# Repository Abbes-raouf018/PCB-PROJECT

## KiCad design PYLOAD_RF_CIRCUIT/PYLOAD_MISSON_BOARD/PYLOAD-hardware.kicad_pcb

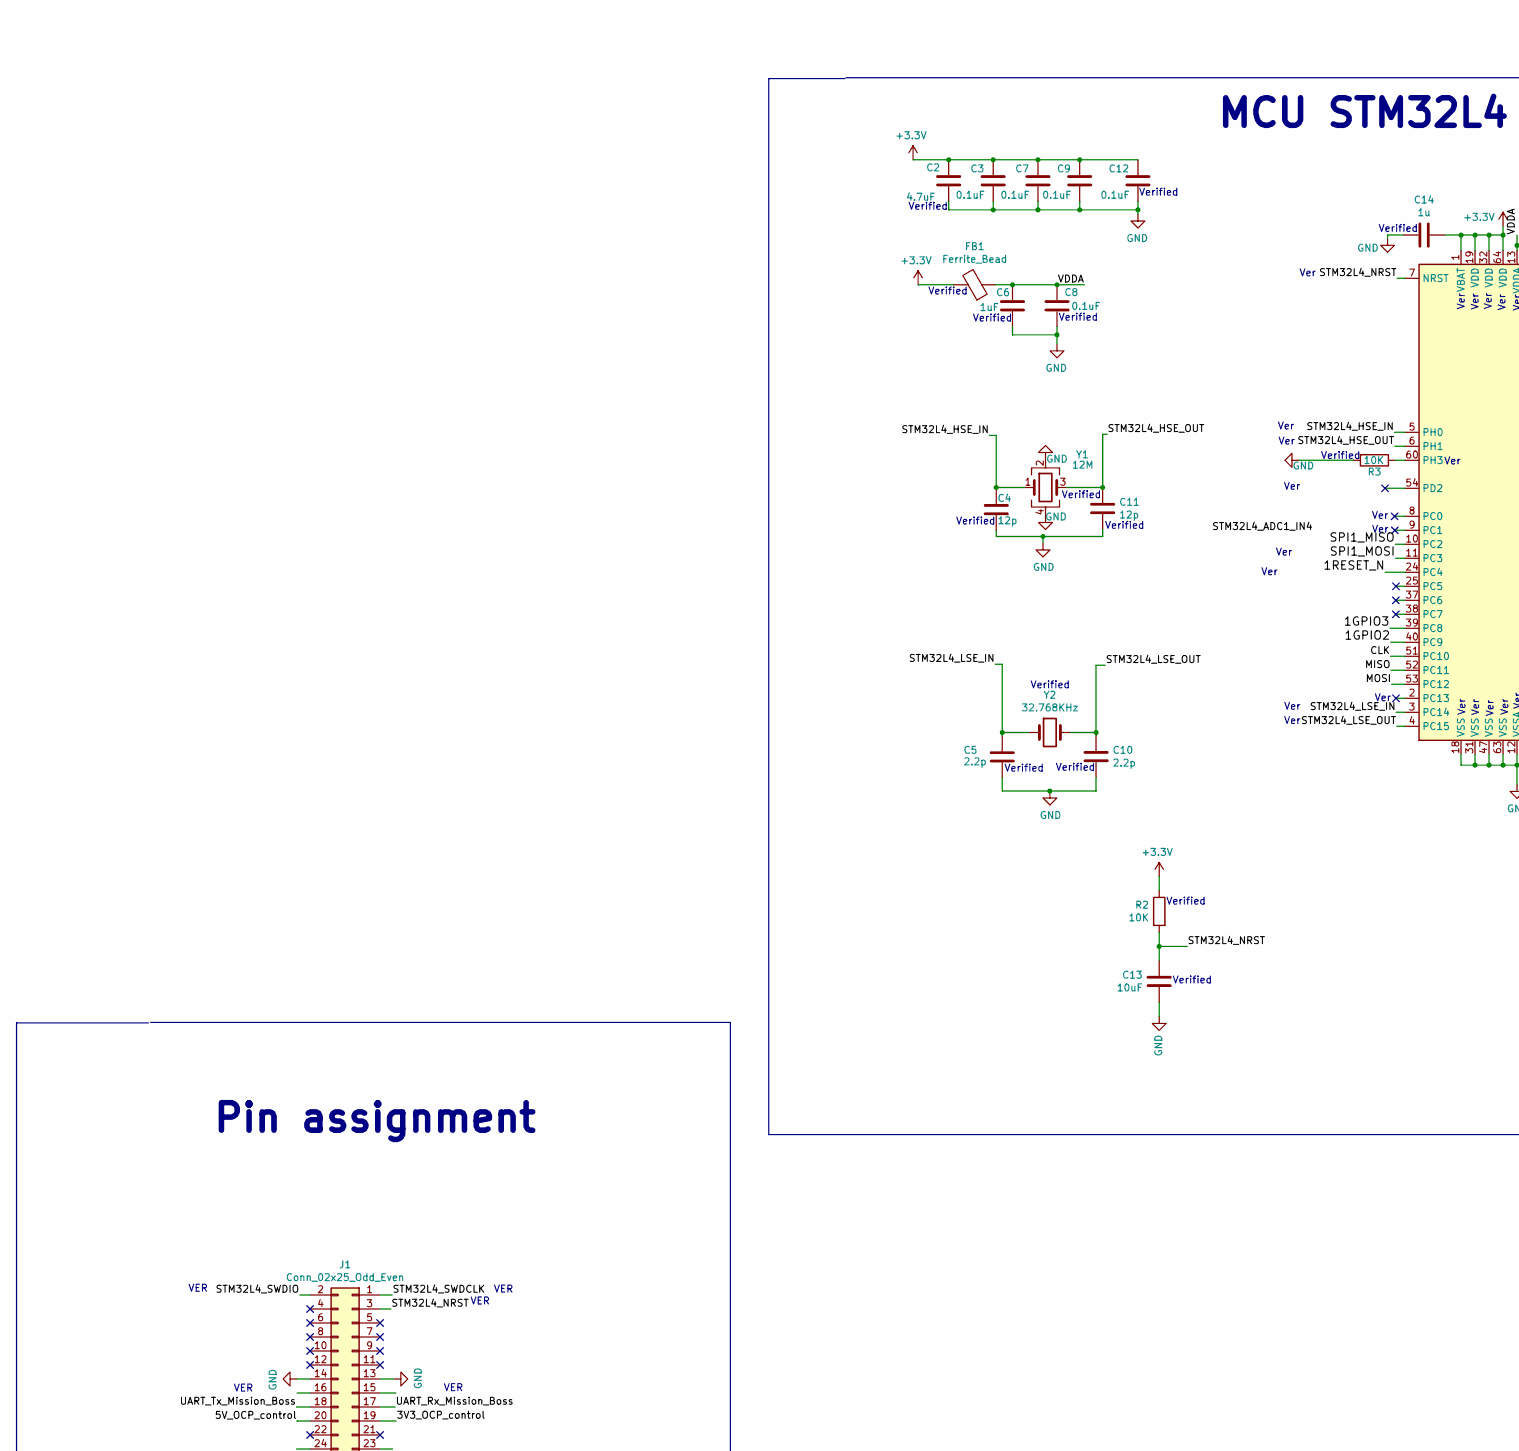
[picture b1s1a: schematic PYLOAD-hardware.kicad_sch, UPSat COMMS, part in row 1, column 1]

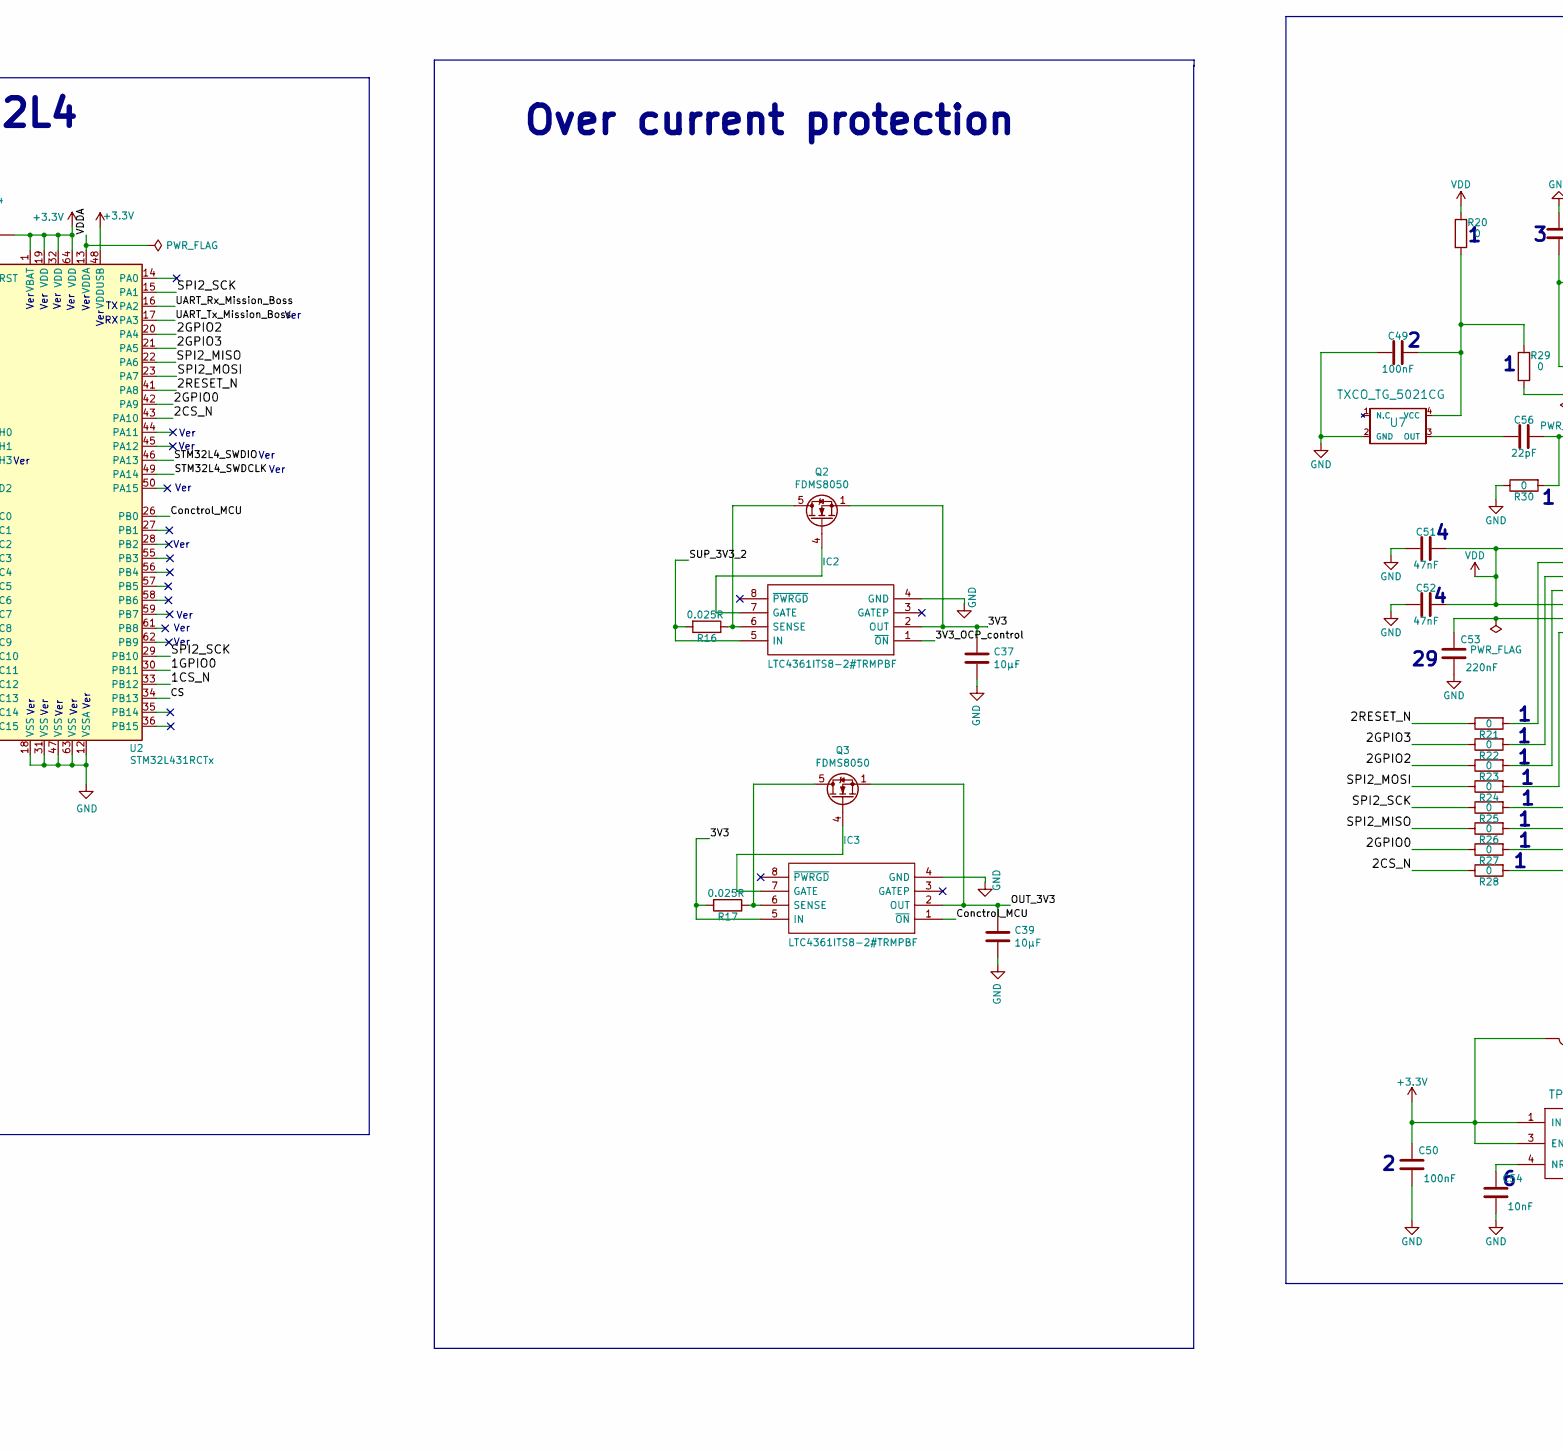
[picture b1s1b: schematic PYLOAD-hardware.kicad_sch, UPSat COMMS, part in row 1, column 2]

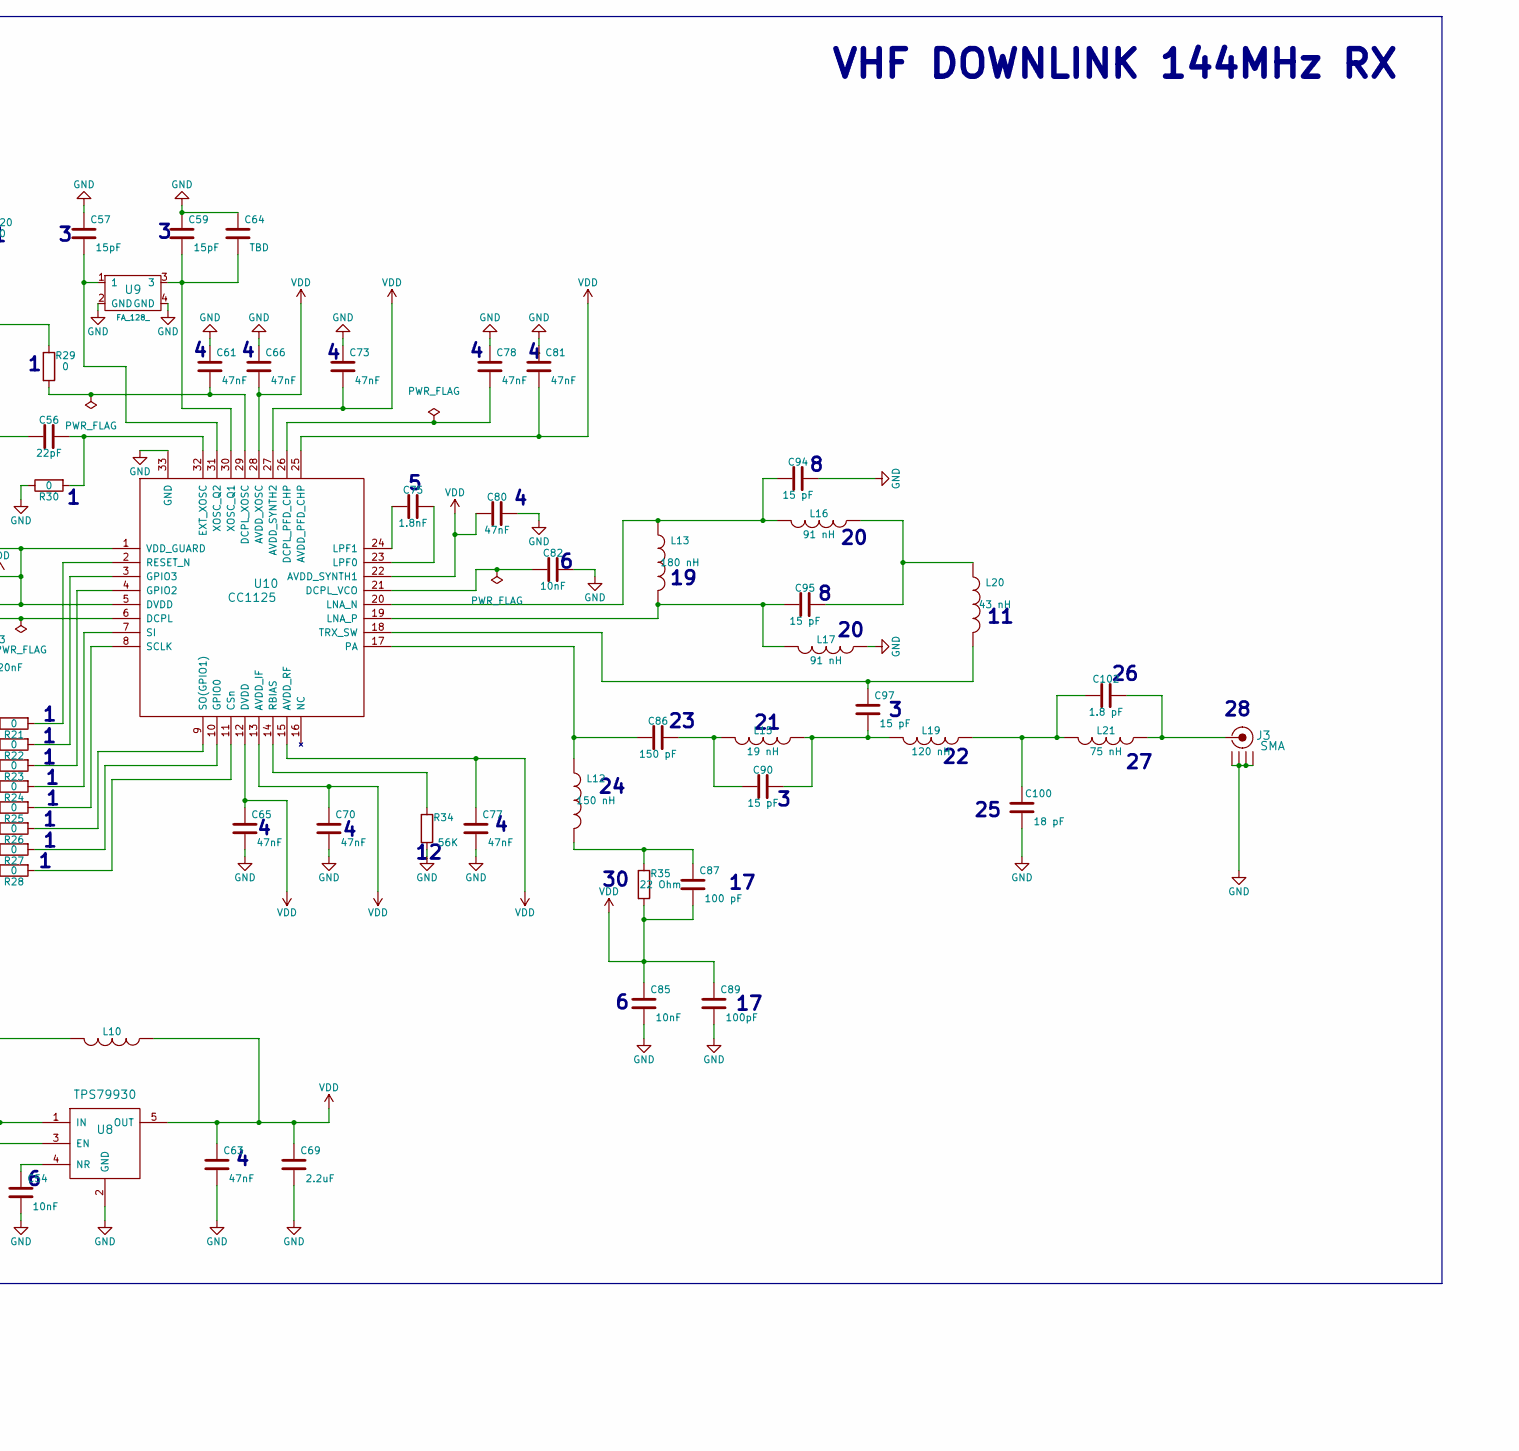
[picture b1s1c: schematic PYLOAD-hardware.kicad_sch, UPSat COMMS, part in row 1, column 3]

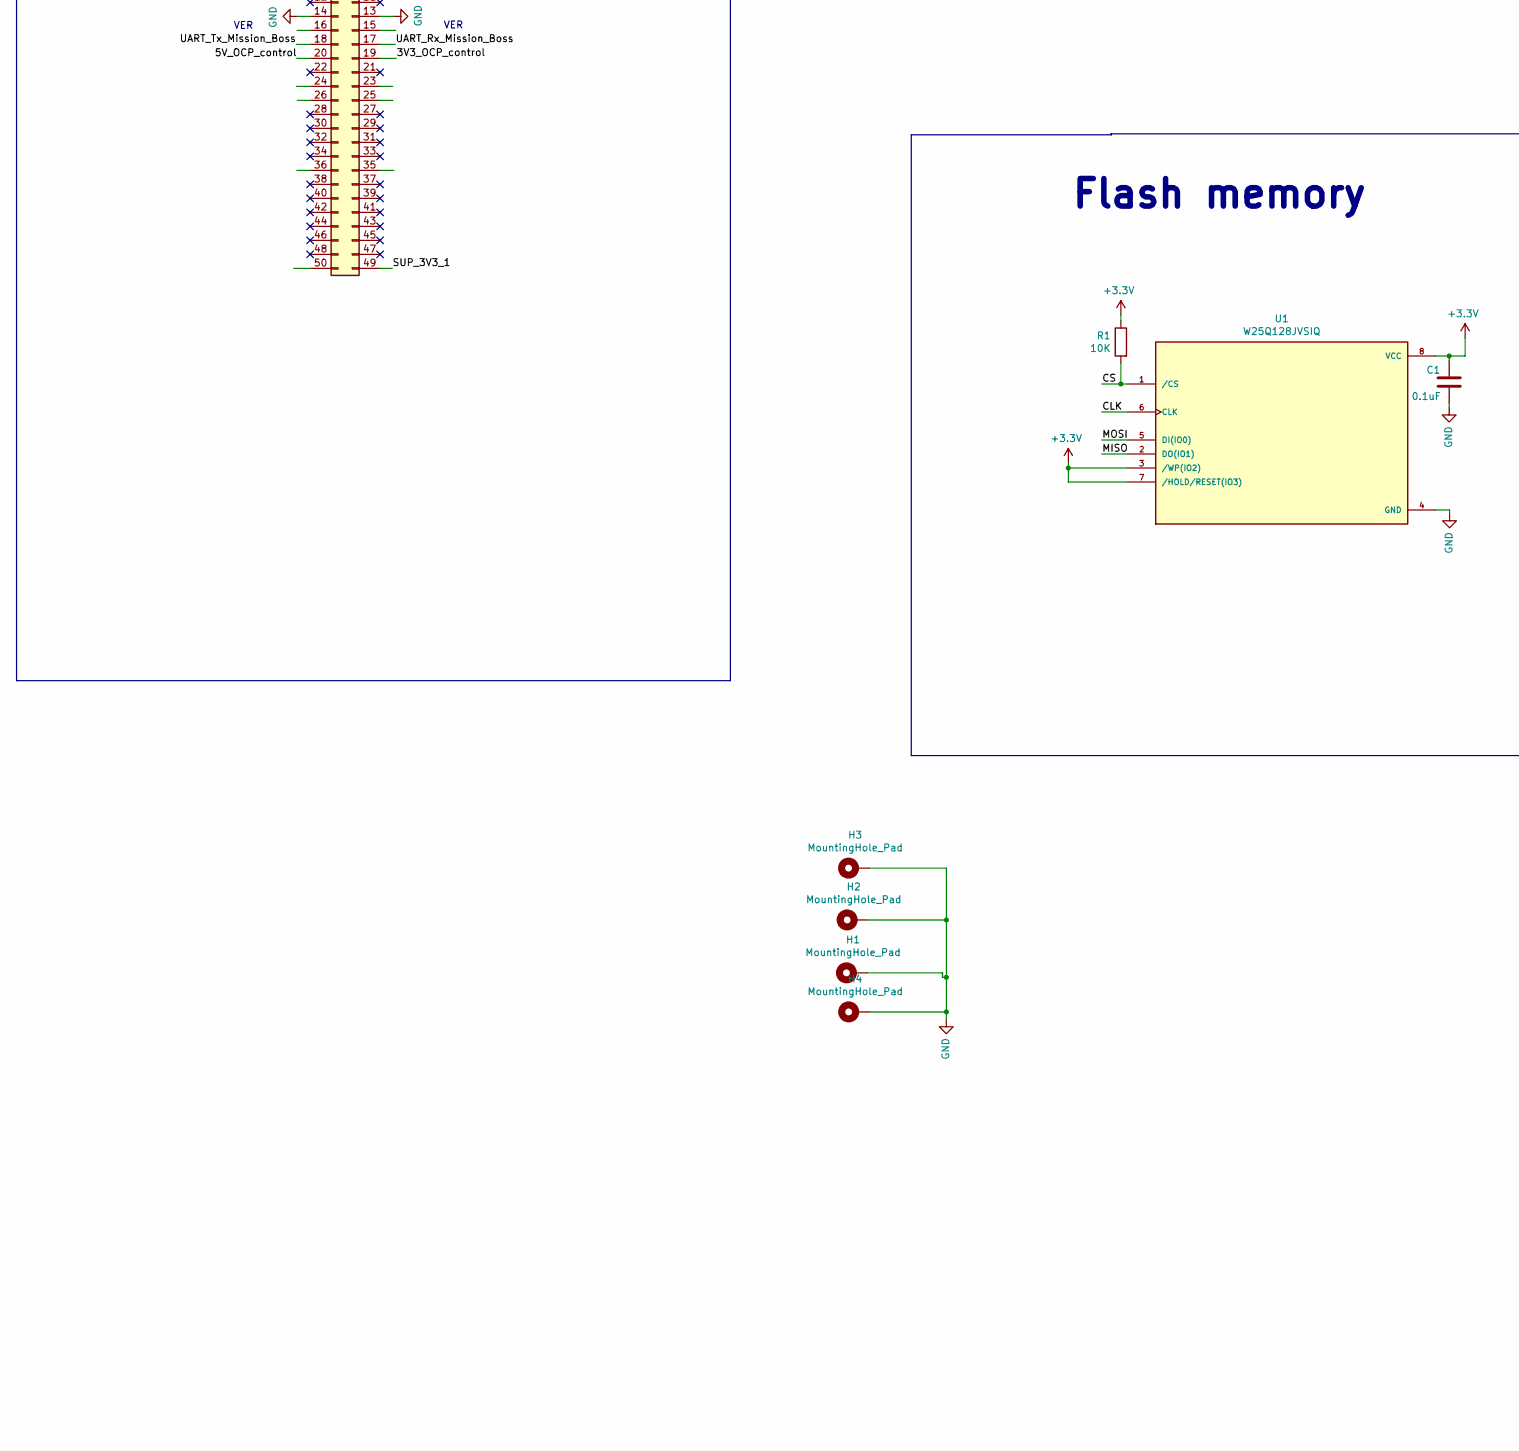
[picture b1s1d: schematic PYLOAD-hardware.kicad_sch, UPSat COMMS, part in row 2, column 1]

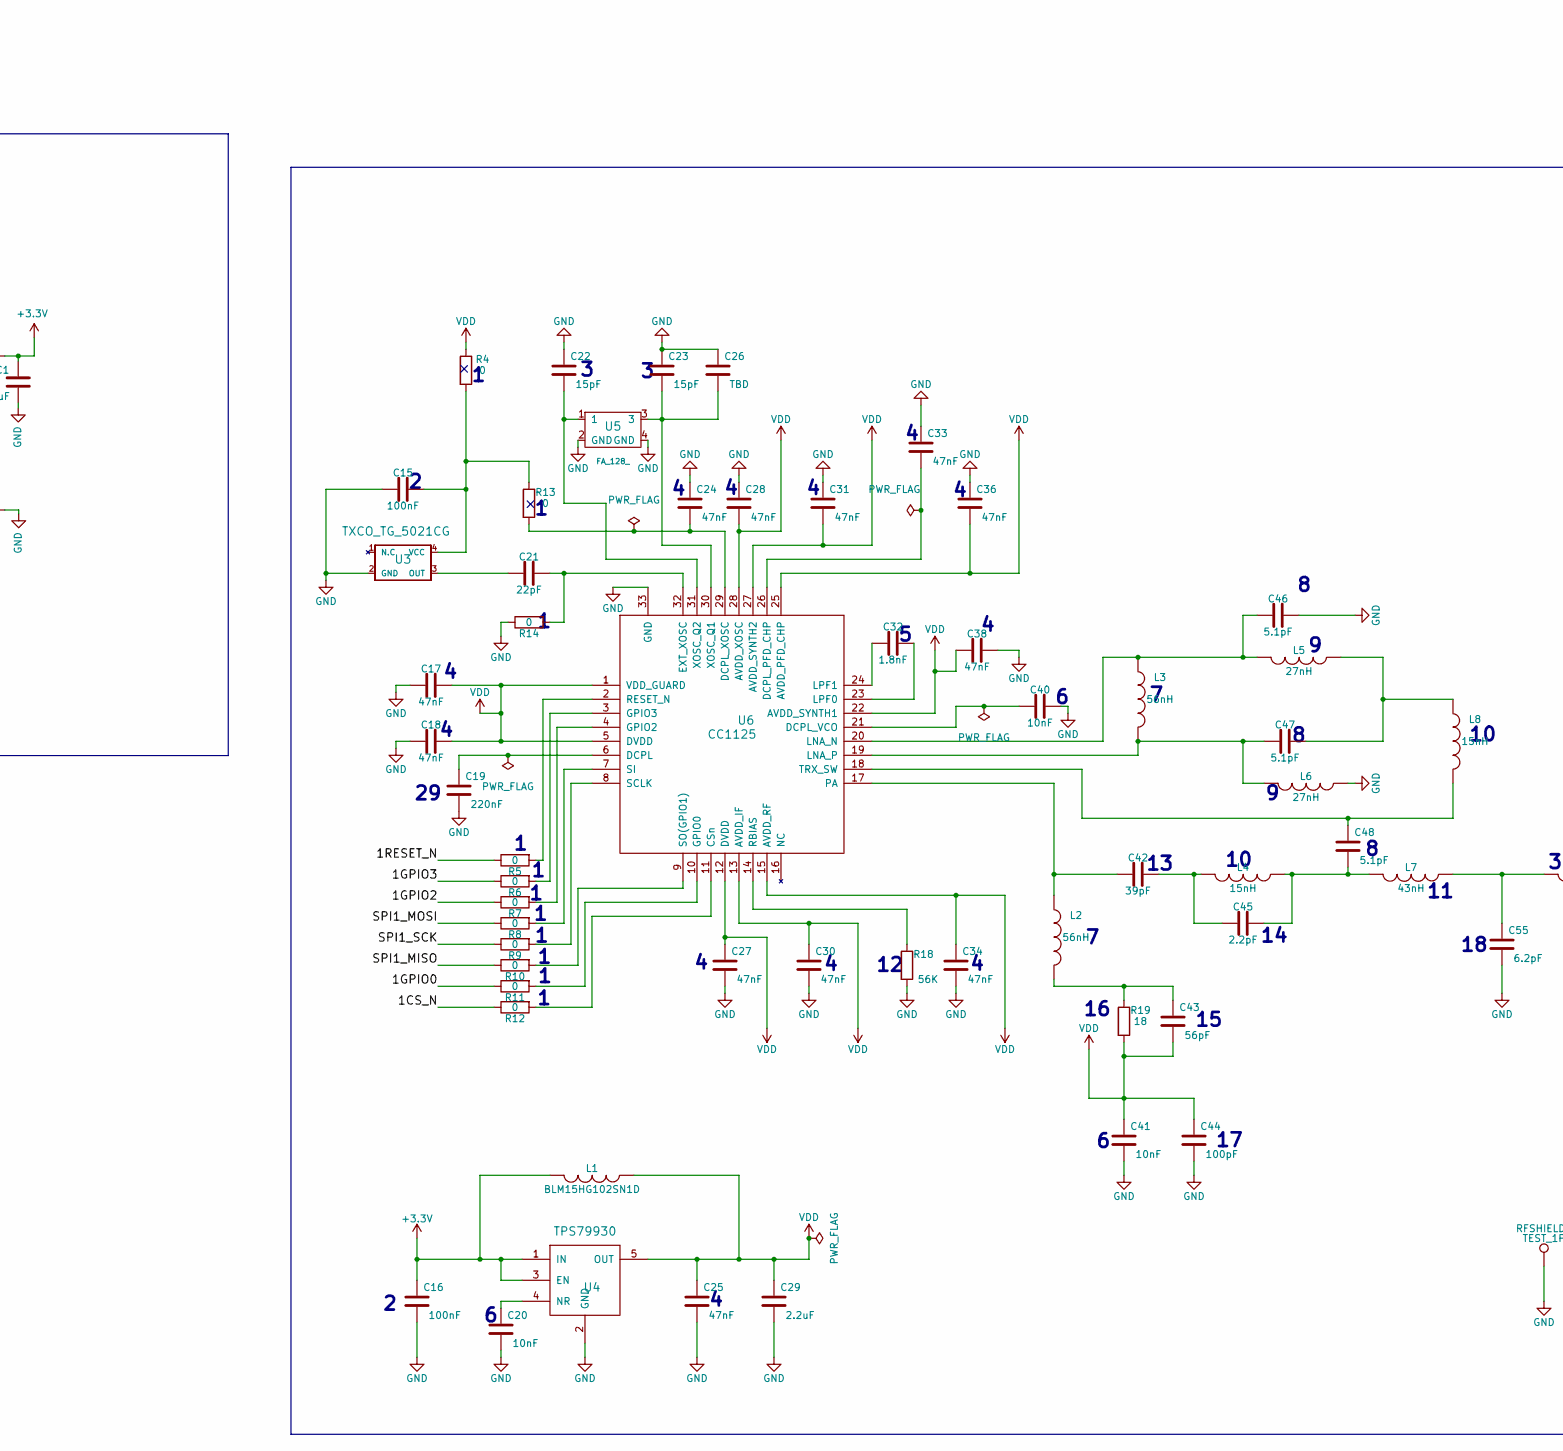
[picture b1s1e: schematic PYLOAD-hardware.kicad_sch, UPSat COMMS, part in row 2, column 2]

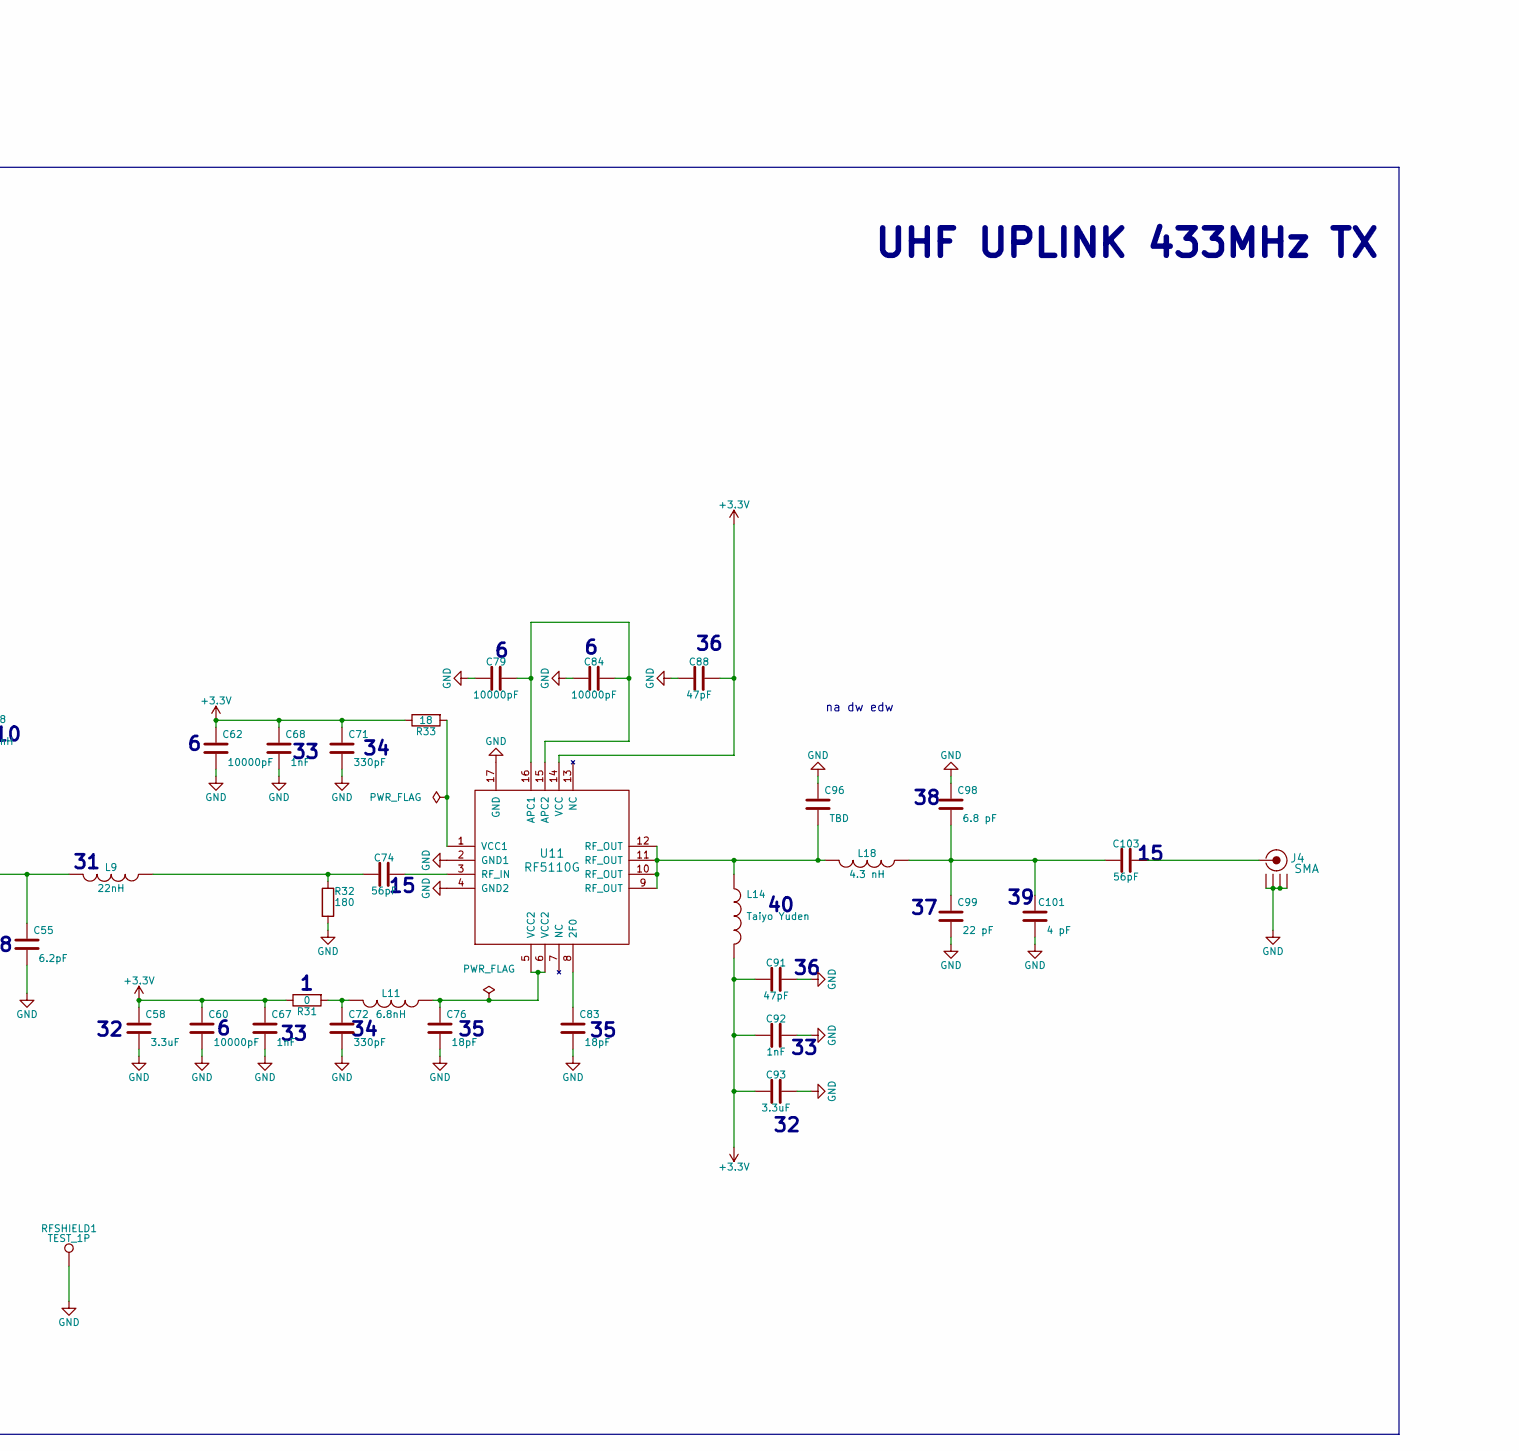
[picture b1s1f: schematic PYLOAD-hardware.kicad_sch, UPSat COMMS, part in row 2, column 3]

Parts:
C1, C3, C7, C9: 0.1uF; C_0402_1005Metric; lCSC C1525
C2: 4.7uF; C_0402_1005Metric; LCSC C23733
C4, C11: 12p; C_0402_1005Metric; LCSC C1547
C5, C10: 2.2p; C_0402_1005Metric; LCSC C1559
C6: 1uF; C_0402_1005Metric; LCSC C52923
C8, C12: 0.1uF; C_0402_1005Metric; LCSC C1525
C13: 10uF; C_0805_2012Metric; LCSC C440198
C14: 1u; C_0402_1005Metric; LCSC C52923
C15, C16, C49, C50: 100nF; C_0402_1005Metric; LCSC C1525
C17, C18, C24, C25, C27, C28, C30, C31, C33, C34, C36, C38, C51, C52, C61, C63, C65, C66, C70, C73, C77, C78, C80, C81: 47nF; C_0402_1005Metric; LCSC C1525
C19, C53: 220nF; C_0402_1005Metric; LCSC C1525
C20, C40, C41, C54, C82, C85: 10nF; C_0402_1005Metric; LCSC C1525
C21, C56: 22pF; C_0402_1005Metric; LCSC C1525
C22, C23, C57, C59: 15pF; C_0402_1005Metric; LCSC C1525
C26, C64, C96: TBD; C_0402_1005Metric; LCSC C1525
C29, C69: 2.2uF; C_0603_1608Metric; LCSC C1679
C32, C75: 1.8nF; C_0402_1005Metric; LCSC C1525
C37, C39: 10µF; C_0402_1005Metric; LCSC C1547
C42: 39pF; C_0402_1005Metric; LCSC C1525
C43, C74, C103: 56pF; C_0402_1005Metric; LCSC C1525
C44, C89: 100pF; C_0402_1005Metric; LCSC C1525
C45: 2.2pF; C_0402_1005Metric; LCSC C1525
C46, C47, C48: 5.1pF; C_0402_1005Metric; LCSC C1525
C55: 6.2pF; C_0402_1005Metric; LCSC C1525
C58, C93: 3.3uF; C_0402_1005Metric; LCSC C1525
C60, C62, C79, C84: 10000pF; C_0402_1005Metric; LCSC C1525
C67, C68, C92: 1nF; C_0402_1005Metric; LCSC C1525
C71, C72: 330pF; C_0402_1005Metric; LCSC C1525
C76, C83: 18pF; C_0402_1005Metric; LCSC C1525
C86: 150 pF; C_0402_1005Metric; LCSC C1525
C87: 100 pF; C_0402_1005Metric; LCSC C1525
C88, C91: 47pF; C_0402_1005Metric; LCSC C1525
C90, C94, C95, C97: 15 pF; C_0402_1005Metric; LCSC C1525
C98: 6.8 pF; C_0402_1005Metric; LCSC C1525
C99: 22 pF; C_0402_1005Metric; LCSC C1525
C100: 18 pF; C_0402_1005Metric; LCSC C1525
C101: 4 pF; C_0402_1005Metric; LCSC C1525
C102: 1.8 pF; C_0402_1005Metric; LCSC C1525
FB1: Ferrite_Bead; L_0603_1608Metric; LCSC C20345
H1, H2, H3, H4: MountingHole_Pad; MountingHole_3.7mm
IC2, IC3: LTC4361ITS8-2#TRMPBF; Mouser Part Number 584-C4361ITS8-2TMPF
J1: Conn_02x25_Odd_Even; HDR-TH_50P-P2.00-V-M-R2-C25-S2.00; LCSC C725937
J3, J4: SMA; 60611002111502
L1: BLM15HG102SN1D; C_0402_1005Metric; LCSC C76889
L2, L3: 56nH; L_01005_0402Metric; LCSC C76889
L4: 15nH; L_01005_0402Metric; LCSC C76899
L5, L6: 27nH; L_01005_0402Metric; LCSC C76889
L7: 43nH; L_01005_0402Metric; LCSC C76889
L8: 15nH; L_01005_0402Metric; LCSC C76889
L9: 22nH; L_01005_0402Metric; LCSC C76889
L10: Capacitor_SMD:C_0402_1005Metric; C_0402_1005Metric; LCSC C76889
L11: 6.8nH; L_01005_0402Metric; LCSC C76889
L12: 150 nH; L_01005_0402Metric; LCSC C76889
L13: 180 nH; L_01005_0402Metric; LCSC C76889
L14: Taiyo Yuden; L_01005_0402Metric; LCSC C76889
L15: 19 nH; L_01005_0402Metric; LCSC C76889
L16, L17: 91 nH; L_01005_0402Metric; LCSC C76889
L18: 4.3 nH; L_01005_0402Metric; LCSC C76889
L19: 120 nH; L_01005_0402Metric; LCSC C76889
L20: 43 nH; L_01005_0402Metric; LCSC C76889
L21: 75 nH; L_01005_0402Metric; LCSC C76889
Q2: FDMS8050; MOSFET_C124530_JLCPCB_REVERSE-POLARITY.kicad_mod; LCSC C150470
Q3: FDMS8050; SOT-323_SC-70; LCSC C150470
R1, R2, R3: 10K; R_0603_1608Metric; LCSC C25804
R4, R5, R6, R7, R8, R9, R10, R11, R12, R13, R14, R20, R21, R22, R23, R24, R25, R26, R27, R28, R30, R31: 0; R_0402_1005Metric; LCSC C25120
R16, R17: 0.025R; R_0603_1608Metric; LCSC C25804
R18, R34: 56K; R_0402_1005Metric; LCSC C25120
R19, R33: 18; R_0402_1005Metric; LCSC C25120
R29: 0; R_0402_1005Metric
R32: 180; R_0402_1005Metric; LCSC C25120
R35: 22 Ohm; R_0402_1005Metric; LCSC C25120
RFSHIELD1: TEST_1P; BMI-S-x06
U1: W25Q128JVSIQ; FLAHMEMORY; PARTREV I; LCSC C97521
U2: STM32L431RCTx; LQFP-64_10x10mm_P0.5mm; LCSC C92468
U3, U7: TXCO_TG_5021CG; Crystal_SMD_3225-4Pin_3.2x2.5mm; LCSC C50430
U4, U8: TPS79930; TSOT-23-5_L2.9-W1.6-P0.95-LS2.8-BL; LCSC C201712
U5, U9: FA_128_; Crystal_SMD_3225-4Pin_3.2x2.5mm; LCSC C50430
U6, U10: CC1125; HVQFN-32_L5.0-W5.0-P0.50-TL-EP; LCSC C133234
U11: RF5110G; QFN-16_L3.0-W3.0-P0.50-BL-EP1.5; LCSC C471155
Y1: 12M; Crystal_SMD_3225-4Pin_3.2x2.5mm; LCSC C50430
Y2: 32.768KHz; Crystal_SMD_3215-2Pin_3.2x1.5mm; LCSC C94673

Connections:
+3V3: C1.1, C2.1, C3.1, C7.1, C9.1, C12.1, C14.1, C16.1, C50.1, C58.1, C60.1, C62.1, C67.1, C68.1, C71.1, C88.1, C91.2, C92.2, C93.2, FB1.2, L1.2, L10.2, L14.2, R1.1, R2.1, R31.1, R33.1, U1.3 (/WP(IO2)), U1.7 (/HOLD/RESET(IO3)), U1.8 (VCC), U2.1 (VBAT), U2.19 (VDD), U2.32 (VDD), U2.48 (VDDUSB), U2.64 (VDD), U4.1 (IN), U4.3 (EN), U8.1 (IN), U8.3 (EN), U11.14 (VCC)
/1CS_N: R12.1, U2.33 (PB12)
/1GPIO0: R11.1, U2.30 (PB11)
/1GPIO2: R7.1, U2.40 (PC9)
/1GPIO3: R6.1, U2.39 (PC8)
/1RESET_N: R5.1, U2.24 (PC4)
/2CS_N: R28.1, U2.43 (PA10)
/2GPIO0: R27.1, U2.42 (PA9)
/2GPIO2: R23.1, U2.20 (PA4)
/2GPIO3: R22.1, U2.21 (PA5)
/2RESET_N: R21.1, U2.41 (PA8)
/3V3: C37.1, IC2.2 (OUT), IC3.5 (IN), Q2.1 (S), Q2.2 (S), Q2.3 (S), R17.2
/3V3_OCP_control: IC2.1 (~ON), J1.19
/5V_OCP_control: J1.20
/CLK: U1.6 (CLK), U2.51 (PC10)
/CS: R1.2, U1.1 (/CS), U2.34 (PB13)
/Conctrol_MCU: IC3.1 (~ON), U2.26 (PB0)
/MISO: U1.2 (DO(IO1)), U2.52 (PC11)
/MOSI: U1.5 (DI(IO0)), U2.53 (PC12)
/OUT_3V3: C39.1, IC3.2 (OUT), Q3.1 (S), Q3.2 (S), Q3.3 (S)
/SPI1_MISO: R10.1, U2.10 (PC2)
/SPI1_MOSI: R8.1, U2.11 (PC3)
/SPI1_SCK: R9.1
/SPI2_MISO: R26.1, U2.22 (PA6)
/SPI2_MOSI: R24.1, U2.23 (PA7)
/SPI2_SCK: R25.1, U2.15 (PA1), U2.29 (PB10)
/STM32L4_HSE_IN: C4.1, U2.5 (PH0), Y1.1
/STM32L4_HSE_OUT: C11.1, U2.6 (PH1), Y1.3
/STM32L4_LSE_IN: C5.1, U2.3 (PC14), Y2.1
/STM32L4_LSE_OUT: C10.1, U2.4 (PC15), Y2.2
/STM32L4_NRST: C13.1, J1.3, R2.2, U2.7 (NRST)
/STM32L4_SWDCLK: J1.1, U2.49 (PA14)
/STM32L4_SWDIO: J1.2, U2.46 (PA13)
/SUP_3V3_1: J1.49, J1.50
/SUP_3V3_2: IC2.5 (IN), J1.25, J1.26, R16.2
/SUP_5V0: J1.15, J1.16; also elsewhere on the board
/SUP_UNREG_1: J1.23, J1.24
/SUP_UNREG_2: J1.35, J1.36
/UART_Rx_Mission_Boss: J1.17, U2.16 (PA2)
/UART_Tx_Mission_Boss: J1.18, U2.17 (PA3)
/VDDA: C6.1, C8.1, FB1.1, U2.13 (VDDA)
GND: C1.2, C2.2, C3.2, C4.2, C5.2, C6.2, C7.2, C8.2, C9.2, C10.2, C11.2, C12.2, C13.2, C14.2, C15.2, C16.2, C17.2, C18.2, C19.2, C20.2, C22.1, C23.1, C24.1, C25.2, C26.1, C27.2, C28.1, C29.2, C30.2, C31.1, C33.1, C34.2, C36.1, C37.2, C38.1, C39.2, C40.1, C41.2, C44.2, C46.1, C49.2, C50.2, C51.2, C52.2, C53.2, C54.2, C55.2, C57.1, C58.2, C59.1, C60.2, C61.1, C62.2, C63.2, C64.1, C65.2, C66.1, C67.2, C68.2, C69.2, C70.2, C71.2, C72.2, C73.1, C76.2, C77.2, C78.1, C79.2, C80.1, C81.1, C82.1, C83.2, C84.2, C85.2, C88.2, C89.2, C91.1, C92.1, C93.1, C94.1, C96.1, C98.1, C99.2, C100.2, C101.2, H1.1, H2.1, H3.1, H4.1, IC2.4 (GND), IC3.4 (GND), J1.13, J1.14, J3.2 (GND1), J3.3 (GND2), J3.4 (GND3), J3.5 (GND4), J4.2 (GND1), J4.3 (GND2), J4.4 (GND3), J4.5 (GND4), L6.1, L17.1, R3.2, R14.1, R18.2, R30.1, R32.2, R34.2, RFSHIELD1.1, U1.4 (GND), U2.12 (VSSA), U2.18 (VSS), U2.31 (VSS), U2.47 (VSS), U2.63 (VSS), U3.2 (GND), U4.2 (GND), U5.2 (GND), U5.4 (GND), U6.33 (GND), U7.2 (GND), U8.2 (GND), U9.2 (GND), U9.4 (GND), U10.33 (GND), U11.2 (GND1), U11.4 (GND2), U11.17 (GND), Y1.2, Y1.4; also elsewhere on the board
unnamed: C15.1, R4.2, R13.1, U3.4 (VCC)
unnamed: C19.1, U6.6 (DCPL)
unnamed: C20.1, U4.4 (NR)
unnamed: C21.1, R14.2, U6.32 (EXT_XOSC)
unnamed: C21.2, U3.3 (OUT)
unnamed: C22.2, U5.1, U6.31 (XOSC_Q2)
unnamed: C23.2, C26.2, U5.3, U6.30 (XOSC_Q1)
unnamed: C24.2, R13.2, U6.29 (DCPL_XOSC)
unnamed: C32.1, U6.23 (LPF0)
unnamed: C32.2, U6.24 (LPF1)
unnamed: C33.2, U6.26 (DCPL_PFD_CHP)
unnamed: C40.2, U6.21 (DCPL_VCO)
unnamed: C42.1, C45.2, L4.2
unnamed: C42.2, L2.1, U6.17 (PA)
unnamed: C43.1, L2.2, R19.1
unnamed: C45.1, C48.2, L4.1, L7.2
unnamed: C46.2, L3.1, L5.2, U6.20 (LNA_N)
unnamed: C47.1, L5.1, L8.1
unnamed: C47.2, L3.2, L6.2, U6.19 (LNA_P)
unnamed: C48.1, L8.2, U6.18 (TRX_SW)
unnamed: C49.1, R20.2, R29.1, U7.4 (VCC)
unnamed: C53.1, U10.6 (DCPL)
unnamed: C54.1, U8.4 (NR)
unnamed: C55.1, L7.1, L9.2
unnamed: C56.1, R30.2, U10.32 (EXT_XOSC)
unnamed: C56.2, U7.3 (OUT)
unnamed: C57.2, U9.1, U10.31 (XOSC_Q2)
unnamed: C59.2, C64.2, U9.3, U10.30 (XOSC_Q1)
unnamed: C61.2, R29.2, U10.29 (DCPL_XOSC)
unnamed: C72.1, L11.2, R31.2
unnamed: C74.1, U11.3 (RF_IN)
unnamed: C74.2, L9.1, R32.1
unnamed: C75.1, U10.23 (LPF0)
unnamed: C75.2, U10.24 (LPF1)
unnamed: C76.1, L11.1, U11.5 (VCC2), U11.6 (VCC2)
unnamed: C78.2, U10.26 (DCPL_PFD_CHP)
unnamed: C79.1, C84.1, U11.15 (APC2), U11.16 (APC1)
unnamed: C82.2, U10.21 (DCPL_VCO)
unnamed: C83.1, U11.8 (2F0)
unnamed: C86.1, C90.2, L15.2
unnamed: C86.2, L12.1, U10.17 (PA)
unnamed: C87.1, L12.2, R35.1
unnamed: C90.1, C97.2, L15.1, L19.2
unnamed: C94.2, L13.1, L16.2, U10.20 (LNA_N)
unnamed: C95.1, L16.1, L20.1
unnamed: C95.2, L13.2, L17.2, U10.19 (LNA_P)
unnamed: C96.2, L14.1, L18.2, U11.9 (RF_OUT), U11.10 (RF_OUT), U11.11 (RF_OUT), U11.12 (RF_OUT)
unnamed: C97.1, L20.2, U10.18 (TRX_SW)
unnamed: C100.1, C102.2, L19.1, L21.2
unnamed: C98.2, C99.1, C101.1, C103.2, L18.1
unnamed: C102.1, J3.1 (RF), L21.1
unnamed: C103.1, J4.1 (RF)
unnamed: IC2.6 (SENSE), Q2.5 (D), R16.1
unnamed: IC2.7 (GATE), Q2.4 (G)
unnamed: IC3.6 (SENSE), Q3.5 (D), R17.1
unnamed: IC3.7 (GATE), Q3.4 (G)
unnamed: R3.1, U2.60 (PH3)
unnamed: R5.2, U6.2 (RESET_N)
unnamed: R6.2, U6.3 (GPIO3)
unnamed: R7.2, U6.4 (GPIO2)
unnamed: R8.2, U6.7 (SI)
unnamed: R9.2, U6.8 (SCLK)
unnamed: R10.2, U6.9 (SO(GPIO1))
unnamed: R11.2, U6.10 (GPIO0)
unnamed: R12.2, U6.11 (CSn)
unnamed: R18.1, U6.14 (RBIAS)
unnamed: R21.2, U10.2 (RESET_N)
unnamed: R22.2, U10.3 (GPIO3)
unnamed: R23.2, U10.4 (GPIO2)
unnamed: R24.2, U10.7 (SI)
unnamed: R25.2, U10.8 (SCLK)
unnamed: R26.2, U10.9 (SO(GPIO1))
unnamed: R27.2, U10.10 (GPIO0)
unnamed: R28.2, U10.11 (CSn)
unnamed: R33.2, U11.1 (VCC1)
unnamed: R34.1, U10.14 (RBIAS)
VDD: C17.1, C18.1, C25.1, C27.1, C28.2, C29.1, C30.1, C31.2, C34.1, C36.2, C38.2, C41.1, C43.2, C44.1, C51.1, C52.1, C63.1, C65.1, C66.2, C69.1, C70.1, C73.2, C77.1, C80.2, C81.2, C85.1, C87.2, C89.1, L1.1, L10.1, R4.1, R19.2, R20.1, R35.2, U4.5 (OUT), U6.1 (VDD_GUARD), U6.5 (DVDD), U6.12 (DVDD), U6.13 (AVDD_IF), U6.15 (AVDD_RF), U6.22 (AVDD_SYNTH1), U6.25 (AVDD_PFD_CHP), U6.27 (AVDD_SYNTH2), U6.28 (AVDD_XOSC), U8.5 (OUT), U10.1 (VDD_GUARD), U10.5 (DVDD), U10.12 (DVDD), U10.13 (AVDD_IF), U10.15 (AVDD_RF), U10.22 (AVDD_SYNTH1), U10.25 (AVDD_PFD_CHP), U10.27 (AVDD_SYNTH2), U10.28 (AVDD_XOSC)

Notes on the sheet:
Verified
na dw edw
Ver
VER
Pin assignment
MCU STM32L4
Flash memory
UHF UPLINK 433MHz TX
VHF DOWNLINK 144MHz RX
Over current protection

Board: 4 copper layers, 184 parts (1 on the bottom side), 115 nets, no tracks yet.

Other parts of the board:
C35: 10µF; C_0402_1005Metric
R15: 0.025R; R_0603_1608Metric

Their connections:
/SUP_5V0: R15.2; also elsewhere on the board
GND: C35.2; also elsewhere on the board

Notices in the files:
PYLOAD_RF_CIRCUIT/PYLOAD_MISSON_BOARD/PYLOAD-hardware.kicad_pcb:
Copyright © 2023
